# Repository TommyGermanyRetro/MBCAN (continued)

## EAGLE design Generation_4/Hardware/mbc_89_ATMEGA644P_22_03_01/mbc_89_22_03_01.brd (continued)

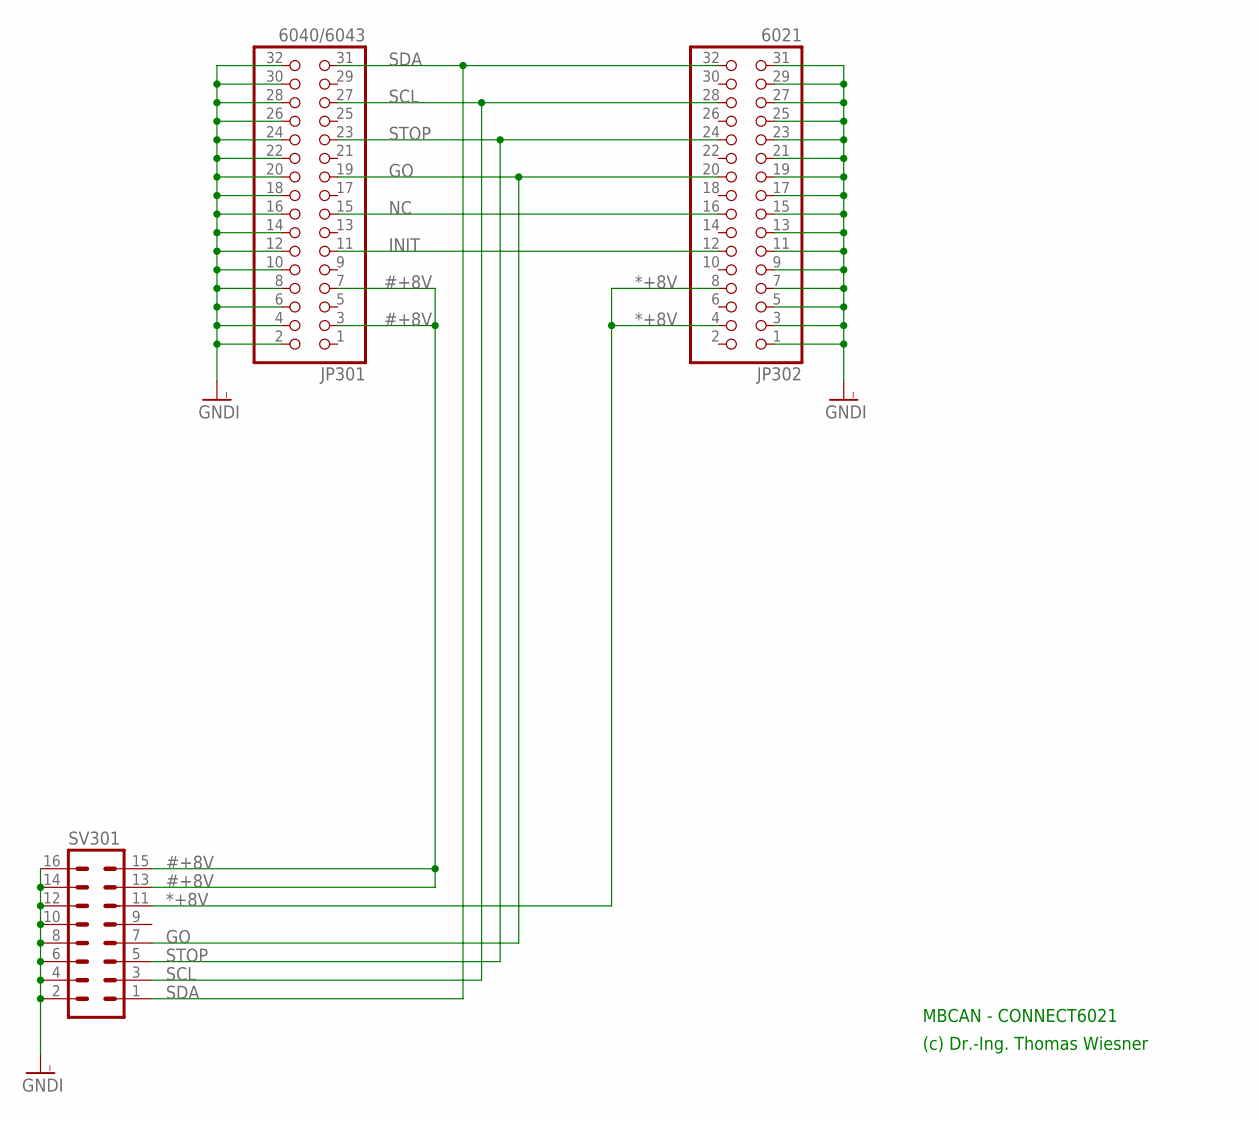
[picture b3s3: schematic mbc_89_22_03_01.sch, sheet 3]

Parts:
JP301: 6040/6043; 2X16
JP302: 6021; 2X16
SV301: ML16

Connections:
#+8V: JP301.3, JP301.7, SV301.13, SV301.15
*+8V: JP302.4, JP302.8, SV301.11
GNDI: JP301.2, JP301.4, JP301.6, JP301.8, JP301.10, JP301.12, JP301.14, JP301.16, JP301.18, JP301.20, JP301.22, JP301.24, JP301.26, JP301.28, JP301.30, JP301.32, JP302.1, JP302.3, JP302.5, JP302.7, JP302.9, JP302.11, JP302.13, JP302.15, JP302.17, JP302.19, JP302.21, JP302.23, JP302.25, JP302.27, JP302.29, JP302.31, SV301.2, SV301.4, SV301.6, SV301.8, SV301.10, SV301.12, SV301.14, SV301.16
GO: JP301.19, JP302.20, SV301.7
INIT: JP301.11, JP302.12
NC: JP301.15, JP302.16
SCL: JP301.27, JP302.28, SV301.3
SDA: JP301.31, JP302.32, SV301.1
STOP: JP301.23, JP302.24, SV301.5

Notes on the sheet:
(c) Dr.-Ing. Thomas Wiesner
MBCAN - CONNECT6021

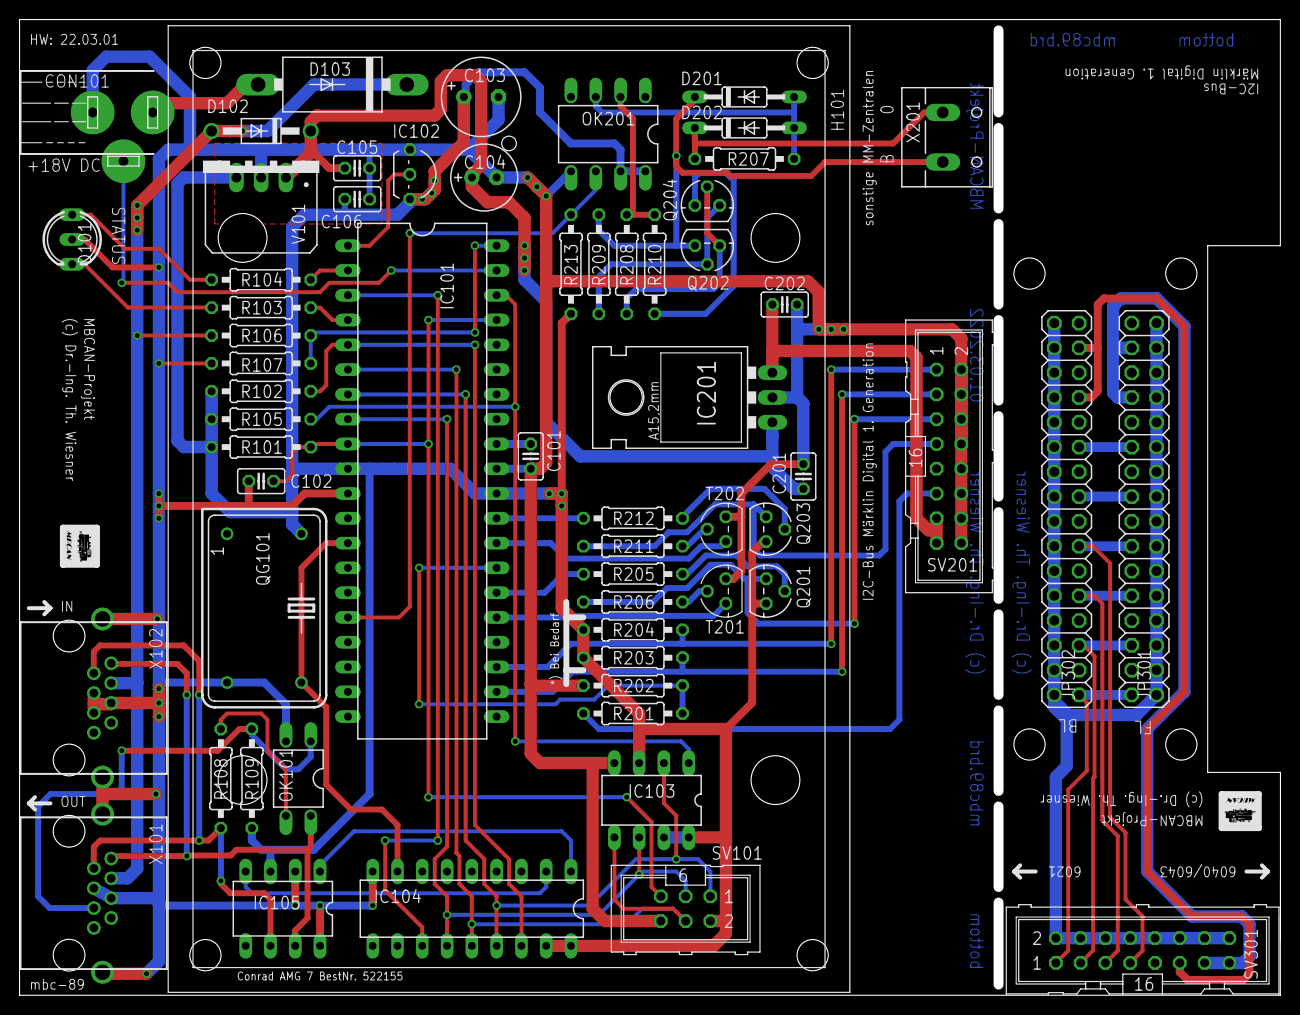
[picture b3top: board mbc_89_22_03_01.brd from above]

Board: 2 copper layers, 129.2 x 100.0 mm, 61 parts (0 on the bottom side), 59 nets.

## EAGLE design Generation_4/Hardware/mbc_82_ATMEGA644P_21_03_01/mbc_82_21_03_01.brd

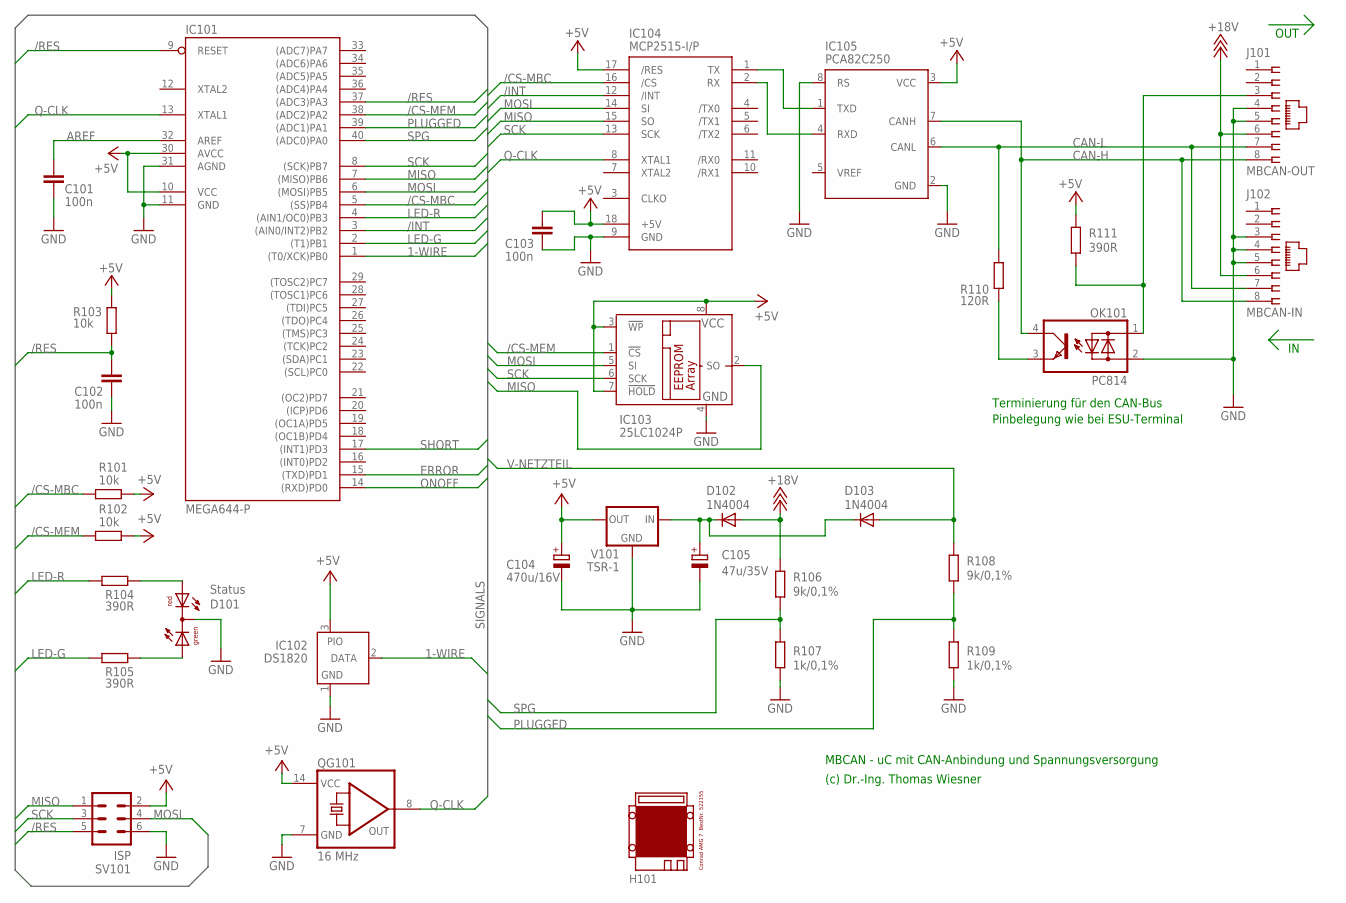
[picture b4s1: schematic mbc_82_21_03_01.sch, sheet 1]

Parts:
C101, C102, C103: 100n; C025-025X050
C104: 470u/16V; E3,5-8
C105: 47u/35V; E2,5-7
D101: Status; DUOLED5MM
D102, D103: 1N4004; DO41-10
H101: MODULGEHÄUSE-AMG-7
IC101: MEGA644-P; DIL40
IC102: DS1820; TO92-
IC103: 25LC1024P; DIL8
IC104: MCP2515-I/P; DIL18
IC105: PCA82C250; DIL08
J101: MBCAN-OUT; 215877-4
J102: MBCAN-IN; 215877-4
OK101: PC814; DIL04
QG101: 16 MHz; DIL14S
R101, R102, R103: 10k; 0207/10
R104, R105, R111: 390R; 0207/10
R106, R108: 9k/0,1%; 0207/10
R107, R109: 1k/0,1%; 0207/10
R110: 120R; 0207/10
SV101: ISP; ML6
V101: TSR-1; TRACO-TSR-1

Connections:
1-WIRE: IC101.1 ((T0/XCK)PB0), IC102.2 (DATA)
+5V: C103.1, C104.+, IC101.10 (VCC), IC101.30 (AVCC), IC102.3 (PIO), IC103.3 (!WP), IC103.7 (!HOLD), IC103.8 (VCC), IC104.17 (/RES), IC104.18 (+5V), IC105.3 (VCC), QG101.14 (VCC), R101.2, R102.1, R103.2, R111.1, SV101.2, V101.OUT; also elsewhere on the board
+18V: D102.A, J101.6, J102.6, R106.1
/CS-MBC: IC101.5 ((SS)PB4), IC104.16 (/CS), R101.1
/CS-MEM: IC101.38 ((ADC2)PA2), IC103.1 (!CS), R102.2
/INT: IC101.3 ((AIN0/INT2)PB2), IC104.12 (/INT)
/RES: C102.1, IC101.9 (RESET), IC101.37 ((ADC3)PA3), R103.1, SV101.5
AREF: C101.1, IC101.32 (AREF)
CAN-H: IC105.7 (CANH), J101.8, J102.8, OK101.4 (C)
CAN-L: IC105.6 (CANL), J101.7, J102.7, R110.2
ERROR: IC101.15 ((TXD)PD1); also elsewhere on the board
GND: C101.2, C102.2, C103.2, C104.-, C105.-, D101.K (C), IC101.11 (GND), IC101.31 (AGND), IC102.1 (GND), IC103.4 (GND), IC104.9 (GND), IC105.2 (GND), IC105.8 (RS), J101.4, J101.5, J102.3, J102.4, J102.5, OK101.2 (AC2), QG101.7 (GND), R107.2, R109.2, SV101.6, V101.GND; also elsewhere on the board
LED-G: IC101.2 ((T1)PB1), R105.1
LED-R: IC101.4 ((AIN1/OC0)PB3), R104.1
MISO: IC101.7 ((MISO)PB6), IC103.2 (SO), IC104.15 (SO), SV101.1
MOSI: IC101.6 ((MOSI)PB5), IC103.5 (SI), IC104.14 (SI), SV101.4
unnamed: IC104.1 (TX), IC105.1 (TXD)
unnamed: IC104.2 (RX), IC105.4 (RXD)
unnamed: OK101.3 (E), R110.1
unnamed: J101.3, OK101.1 (AC1), R111.2
unnamed: C105.+, D102.C, D103.C, V101.IN
unnamed: D101.AR, R104.2
unnamed: D101.AG, R105.2
ONOFF: IC101.14 ((RXD)PD0); also elsewhere on the board
PLUGGED: IC101.39 ((ADC1)PA1), R108.2, R109.1
Q-CLK: IC101.13 (XTAL1), IC104.8 (XTAL1), QG101.8 (OUT)
SCK: IC101.8 ((SCK)PB7), IC103.6 (SCK), IC104.13 (SCK), SV101.3
SHORT: IC101.17 ((INT1)PD3); also elsewhere on the board
SPG: IC101.40 ((ADC0)PA0), R106.2, R107.1
V-NETZTEIL: D103.A, R108.1; also elsewhere on the board

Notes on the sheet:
MBCAN - uC mit CAN-Anbindung und Spannungsversorgung
(c) Dr.-Ing. Thomas Wiesner
Terminierung für den CAN-Bus
Pinbelegung wie bei ESU-Terminal
OUT

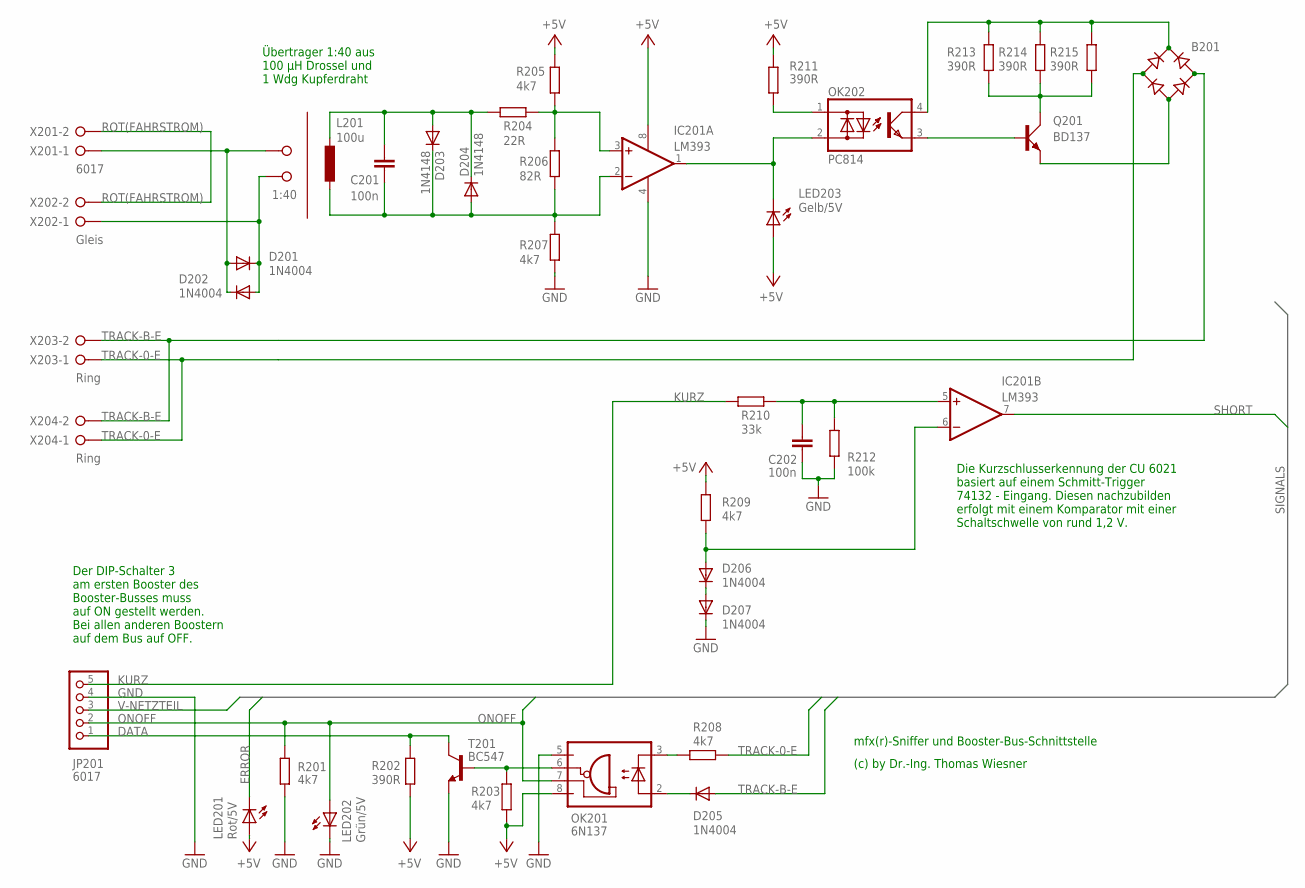
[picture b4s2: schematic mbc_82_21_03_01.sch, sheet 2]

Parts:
B201: RB1A
C201, C202: 100n; C025-025X050
D201, D202, D205, D206, D207: 1N4004; DO41-10
D203, D204: 1N4148; DO35-10
IC201: LM393; DIL08
JP201: 6017; 1X05
L201: 100u; 6000-XXXX-RC
LED201: Rot/5V; LED3MM
LED202: Grün/5V; LED3MM
LED203: Gelb/5V; LED3MM
OK201: 6N137; DIL08
OK202: PC814; DIL04
Q201: BD137; TO126AV
R201, R203, R205, R207, R208, R209: 4k7; 0207/10
R202, R211, R213, R214, R215: 390R; 0207/10
R204: 22R; 0207/10
R206: 82R; 0207/10
R210: 33k; 0207/10
R212: 100k; 0207/10
T201: BC547; TO92
TP: 1:40; W237-132
X201: 6017; W237-132
X202: Gleis; W237-132
X203, X204: Ring; W237-132

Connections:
+5V: IC201.8 (V+), LED201.A, LED203.A, OK201.8 (VCC), R202.1, R203.1, R205.2, R209.2, R211.2; also elsewhere on the board
DATA: JP201.1, R202.2, T201.3 (C)
ERROR: LED201.K (C); also elsewhere on the board
GND: C202.2, D207.C, IC201.4 (V-), JP201.4, LED202.K (C), OK201.5 (GND), R201.2, R207.2, R212.2, T201.1 (E); also elsewhere on the board
KURZ: JP201.5, R210.2
unnamed: OK202.3 (E), Q201.B
unnamed: D205.C, OK201.2 (A)
unnamed: OK201.3 (C), R208.1
unnamed: B201.-, Q201.E
unnamed: C201.2, D203.C, D204.A, IC201.2 (-IN), L201.2, R206.2, R207.1
unnamed: IC201.3 (+IN), R204.2, R205.1, R206.1
unnamed: D201.C, D202.A, TP.1, X202.1
unnamed: B201.+, OK202.4 (C), R213.1, R214.1, R215.1
unnamed: Q201.C, R213.2, R214.2, R215.2
unnamed: C201.1, D203.A, D204.C, L201.1, R204.1
unnamed: D206.C, D207.A
unnamed: OK202.1 (AC1), R211.1
unnamed: IC201.1 (COLOUT), LED203.K (C), OK202.2 (AC2)
unnamed: D206.A, IC201.6 (-IN), R209.1
unnamed: C202.1, IC201.5 (+IN), R210.1, R212.1
unnamed: OK201.6 (VO), R203.2, T201.2 (B)
O': D201.A, D202.C, TP.2, X201.1
ONOFF: JP201.2, LED202.A, OK201.7 (VE), R201.1; also elsewhere on the board
ROT(FAHRSTROM): X201.2, X202.2
SHORT: IC201.7 (COLOUT); also elsewhere on the board
TRACK-0-E: B201.AC1, R208.2, X203.1, X204.1
TRACK-B-E: B201.AC2, D205.A, X203.2, X204.2
V-NETZTEIL: JP201.3; also elsewhere on the board

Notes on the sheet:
Übertrager 1:40 aus 100 µH Drossel und 1 Wdg Kupferdraht
mfx(r)-Sniffer und Booster-Bus-Schnittstelle
(c) by Dr.-Ing. Thomas Wiesner
Der DIP-Schalter 3 am ersten Booster des Booster-Busses muss auf ON gestellt werden. Bei allen anderen Boostern auf dem Bus auf OFF.
Die Kurzschlusserkennung der CU 6021 basiert auf einem Schmitt-Trigger 74132 - Eingang. Diesen nachzubilden erfolgt mit einem Komparator mit einer Schaltschwelle von rund 1,2 V.

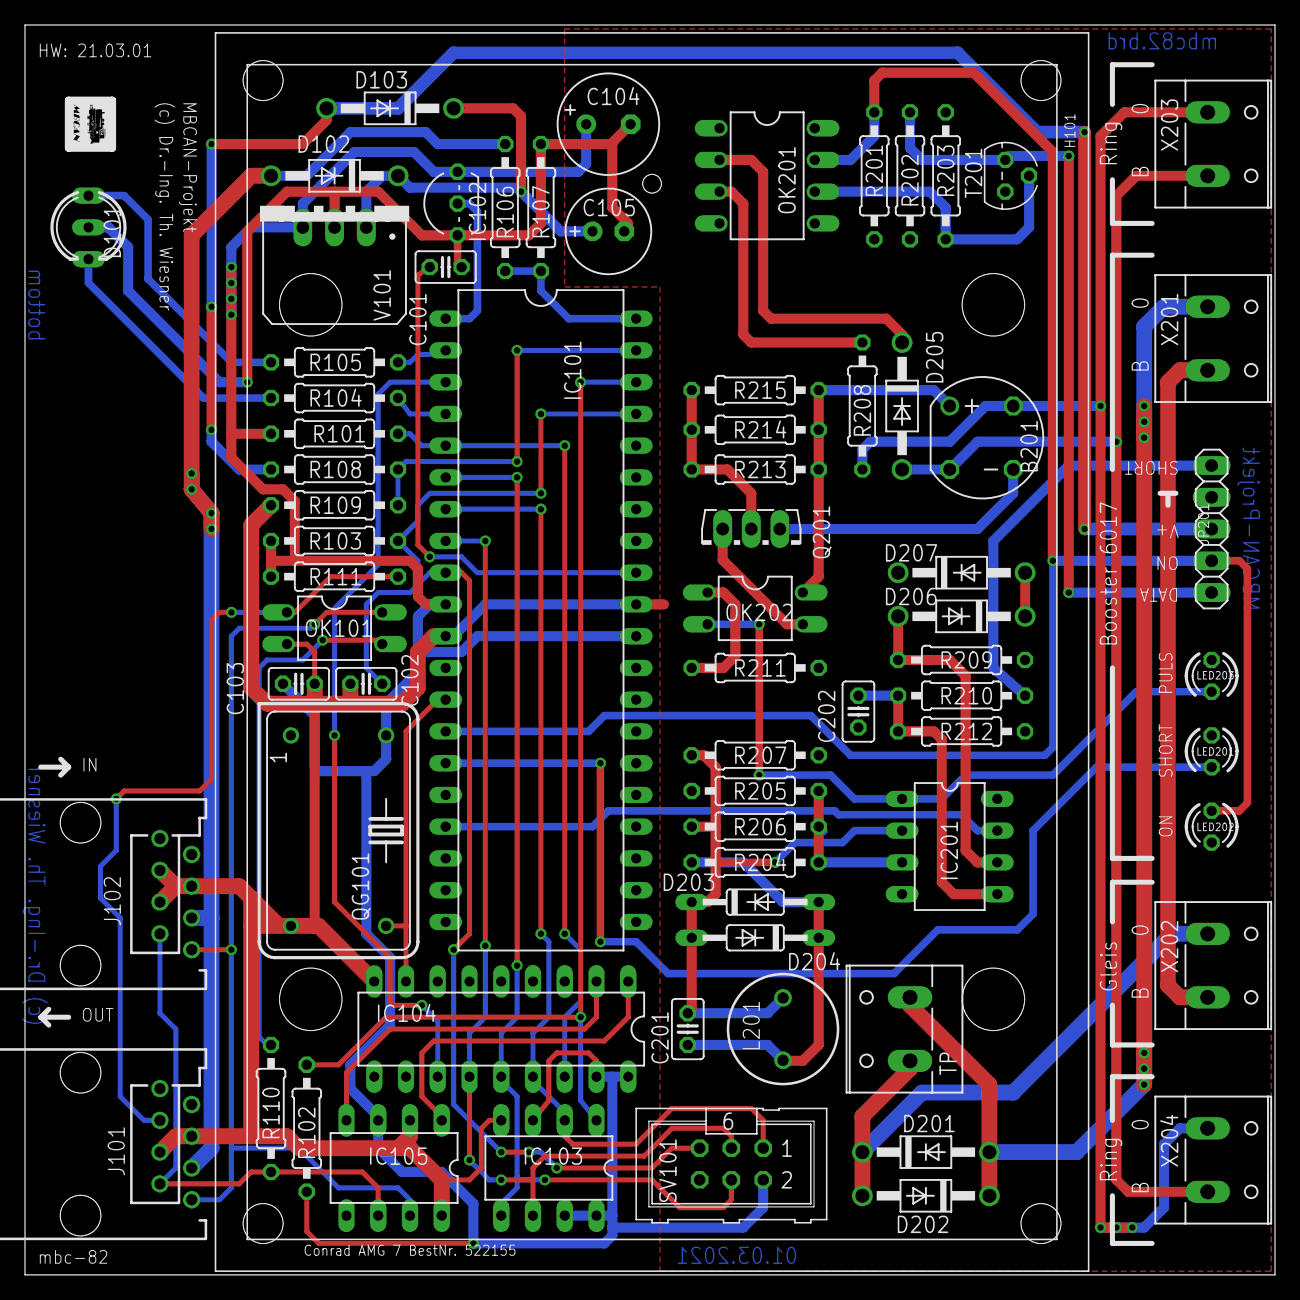
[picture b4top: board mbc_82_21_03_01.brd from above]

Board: 2 copper layers, 100.0 x 100.0 mm, 71 parts (0 on the bottom side), 52 nets.

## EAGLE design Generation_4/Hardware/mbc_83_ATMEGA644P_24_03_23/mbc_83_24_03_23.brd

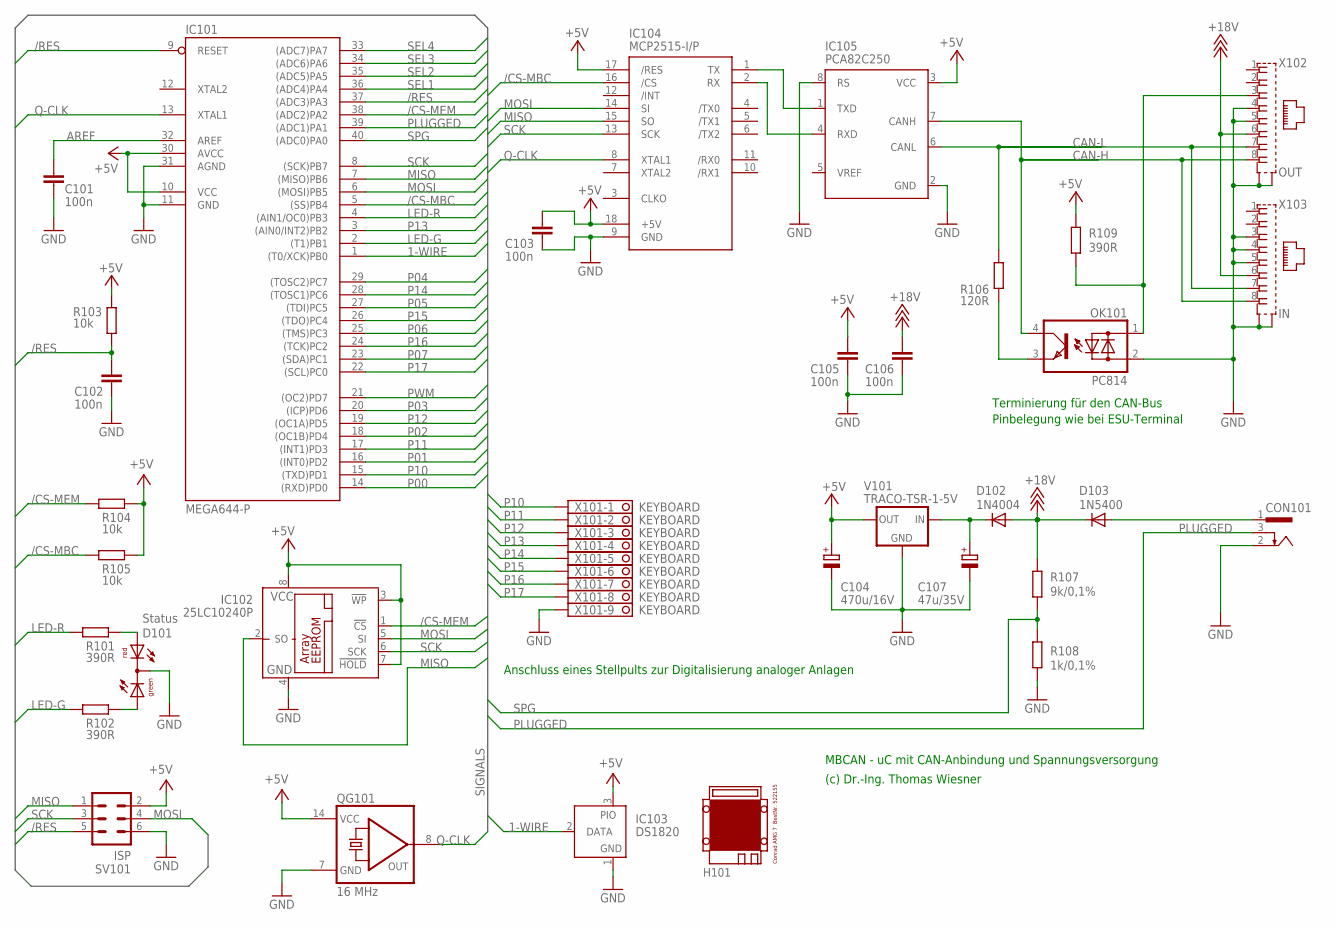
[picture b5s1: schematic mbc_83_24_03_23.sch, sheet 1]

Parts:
C101, C102, C103, C105, C106: 100n; C025-025X050
C104: 470u/16V; E3,5-8
C107: 47u/35V; E2,5-7
CON101: POWER-JACK
D101: Status; DUOLED5MM
D102: 1N4004; DO41-10
D103: 1N5400; DO201-15
H101: MODULGEHÄUSE-AMG-7
IC101: MEGA644-P; DIL40
IC102: 25LC10240P; DIL8
IC103: DS1820; TO92-
IC104: MCP2515-I/P; DIL18
IC105: PCA82C250; DIL08
OK101: PC814; DIL04
QG101: 16 MHz; DIL14S
R101, R102, R109: 390R; 0207/10
R103, R104, R105: 10k; 0207/10
R106: 120R; 0207/10
R107: 9k/0,1%; 0207/10
R108: 1k/0,1%; 0207/10
SV101: ISP; ML6
V101: TRACO-TSR-1-5V; TRACO-TSR-1
X101: KEYBOARD; 1751316
X102: OUT; 0446200002
X103: IN; 0446200002

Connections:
1-WIRE: IC101.1 ((T0/XCK)PB0), IC103.2 (DATA)
+5V: C103.1, C104.+, C105.1, IC101.10 (VCC), IC101.30 (AVCC), IC102.3 (!WP), IC102.7 (!HOLD), IC102.8 (VCC), IC103.3 (PIO), IC104.17 (/RES), IC104.18 (+5V), IC105.3 (VCC), QG101.14 (VCC), R103.2, R104.2, R105.2, R109.1, SV101.2, V101.OUT; also elsewhere on the board
+18V: C106.1, D102.A, D103.C, R107.1, X102.6, X103.6; also elsewhere on the board
/CS-MBC: IC101.5 ((SS)PB4), IC104.16 (/CS), R105.1
/CS-MEM: IC101.38 ((ADC2)PA2), IC102.1 (!CS), R104.1
/RES: C102.1, IC101.9 (RESET), IC101.37 ((ADC3)PA3), R103.1, SV101.5
AREF: C101.1, IC101.32 (AREF)
CAN-H: IC105.7 (CANH), OK101.4 (C), X102.8, X103.8
CAN-L: IC105.6 (CANL), R106.2, X102.7, X103.7
GND: C101.2, C102.2, C103.2, C104.-, C105.2, C106.2, C107.-, CON101.2, D101.K (C), IC101.11 (GND), IC101.31 (AGND), IC102.4 (GND), IC103.1 (GND), IC104.9 (GND), IC105.2 (GND), IC105.8 (RS), OK101.2 (AC2), QG101.7 (GND), R108.2, SV101.6, V101.GND, X101.9, X102.4, X102.5, X102.S@1 (S1), X102.S@2 (S2), X103.3, X103.4, X103.5, X103.S@1 (S1), X103.S@2 (S2); also elsewhere on the board
LED-G: IC101.2 ((T1)PB1), R102.1
LED-R: IC101.4 ((AIN1/OC0)PB3), R101.1
MISO: IC101.7 ((MISO)PB6), IC102.2 (SO), IC104.15 (SO), SV101.1
MOSI: IC101.6 ((MOSI)PB5), IC102.5 (SI), IC104.14 (SI), SV101.4
unnamed: IC104.1 (TX), IC105.1 (TXD)
unnamed: IC104.2 (RX), IC105.4 (RXD)
unnamed: OK101.3 (E), R106.1
unnamed: OK101.1 (AC1), R109.2, X102.3
unnamed: C107.+, D102.C, V101.IN
unnamed: D101.AR, R101.2
unnamed: D101.AG, R102.2
P00: IC101.14 ((RXD)PD0); also elsewhere on the board
P01: IC101.16 ((INT0)PD2); also elsewhere on the board
P02: IC101.18 ((OC1B)PD4); also elsewhere on the board
P03: IC101.20 ((ICP)PD6); also elsewhere on the board
P04: IC101.29 ((TOSC2)PC7); also elsewhere on the board
P05: IC101.27 ((TDI)PC5); also elsewhere on the board
P06: IC101.25 ((TMS)PC3); also elsewhere on the board
P07: IC101.23 ((SDA)PC1); also elsewhere on the board
P10: IC101.15 ((TXD)PD1), X101.1
P11: IC101.17 ((INT1)PD3), X101.2
P12: IC101.19 ((OC1A)PD5), X101.3
P13: IC101.3 ((AIN0/INT2)PB2), X101.4
P14: IC101.28 ((TOSC1)PC6), X101.5
P15: IC101.26 ((TDO)PC4), X101.6
P16: IC101.24 ((TCK)PC2), X101.7
P17: IC101.22 ((SCL)PC0), X101.8
PLUGGED: CON101.3, IC101.39 ((ADC1)PA1)
PWM: IC101.21 ((OC2)PD7); also elsewhere on the board
Q-CLK: IC101.13 (XTAL1), IC104.8 (XTAL1), QG101.8 (OUT)
SCK: IC101.8 ((SCK)PB7), IC102.6 (SCK), IC104.13 (SCK), SV101.3
SEL1: IC101.36 ((ADC4)PA4); also elsewhere on the board
SEL2: IC101.35 ((ADC5)PA5); also elsewhere on the board
SEL3: IC101.34 ((ADC6)PA6); also elsewhere on the board
SEL4: IC101.33 ((ADC7)PA7); also elsewhere on the board
SPG: IC101.40 ((ADC0)PA0), R107.2, R108.1
V-NETZTEIL1: CON101.1, D103.A

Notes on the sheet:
MBCAN - uC mit CAN-Anbindung und Spannungsversorgung
(c) Dr.-Ing. Thomas Wiesner
Terminierung für den CAN-Bus
Pinbelegung wie bei ESU-Terminal
Anschluss eines Stellpults zur Digitalisierung analoger Anlagen

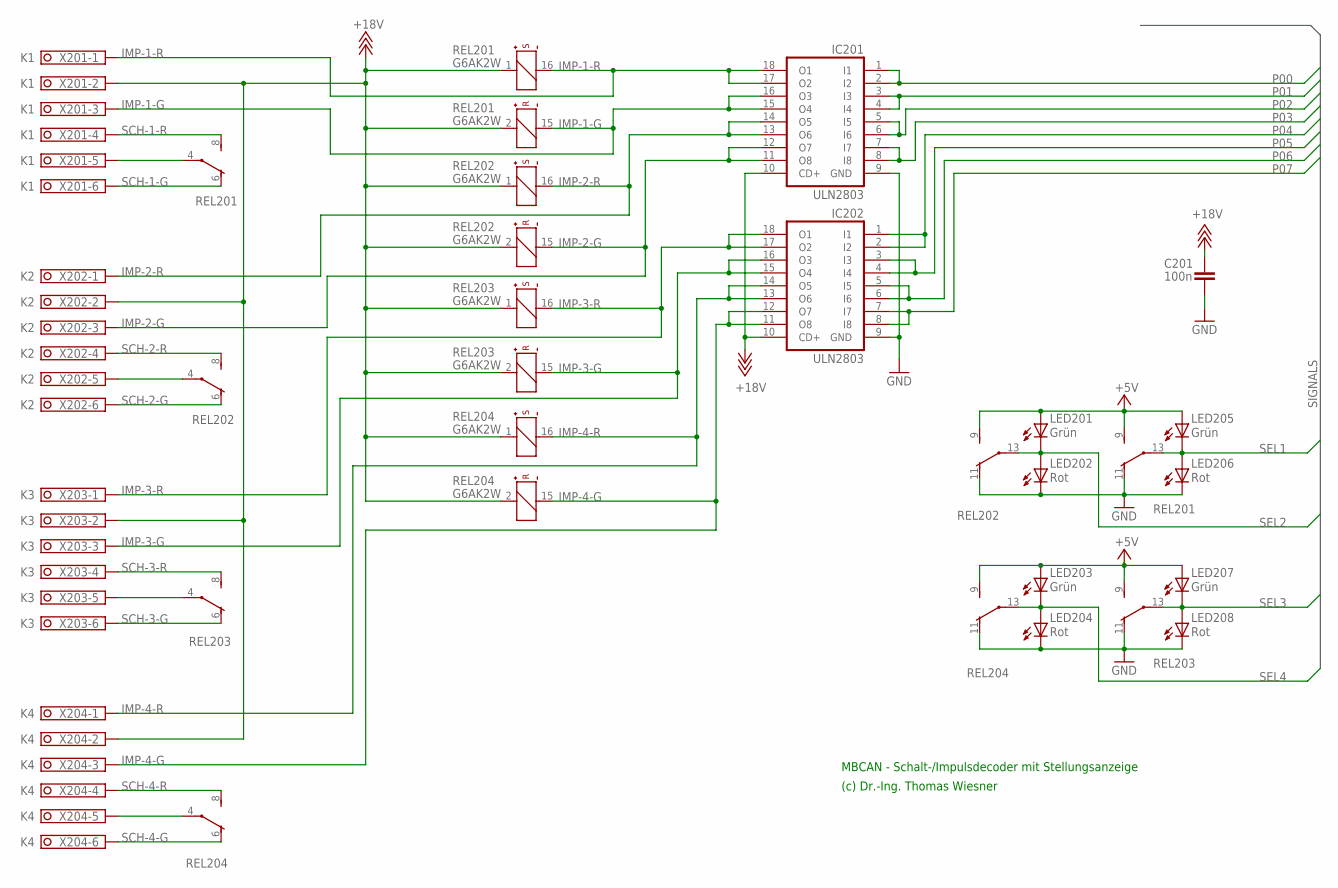
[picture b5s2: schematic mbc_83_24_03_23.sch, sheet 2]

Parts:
C201: 100n; C025-025X050
IC201, IC202: ULN2803; DIL18
LED201, LED203, LED205, LED207: Grün; LED3MM
LED202, LED204, LED206, LED208: Rot; LED3MM
REL201, REL202, REL203, REL204: G6AK2W; REL-BIPOLAR
X201: K1; 1751280
X202: K2; 1751280
X203: K3; 1751280
X204: K4; 1751280

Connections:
+5V: LED201.A, LED203.A, LED205.A, LED207.A, REL201.9 (S), REL202.9 (S), REL203.9 (S), REL204.9 (S); also elsewhere on the board
+18V: C201.1, IC201.10 (CD+), IC202.10 (CD+), REL201.1 (+), REL201.2 (+), REL202.1 (+), REL202.2 (+), REL203.1 (+), REL203.2 (+), REL204.1 (+), REL204.2 (+), X201.2, X202.2, X203.2, X204.2; also elsewhere on the board
GND: C201.2, IC201.9 (GND), IC202.9 (GND), LED202.K (C), LED204.K (C), LED206.K (C), LED208.K (C), REL201.11 (O), REL202.11 (O), REL203.11 (O), REL204.11 (O); also elsewhere on the board
IMP-1-G: IC201.15 (O4), IC201.16 (O3), REL201.15 (-), X201.3; also elsewhere on the board
IMP-1-R: IC201.17 (O2), IC201.18 (O1), REL201.16 (-), X201.1; also elsewhere on the board
IMP-2-G: IC201.11 (O8), IC201.12 (O7), REL202.15 (-), X202.3; also elsewhere on the board
IMP-2-R: IC201.13 (O6), IC201.14 (O5), REL202.16 (-), X202.1; also elsewhere on the board
IMP-3-G: IC202.15 (O4), IC202.16 (O3), REL203.15 (-), X203.3; also elsewhere on the board
IMP-3-R: IC202.17 (O2), IC202.18 (O1), REL203.16 (-), X203.1; also elsewhere on the board
IMP-4-G: IC202.11 (O8), IC202.12 (O7), REL204.15 (-), X204.3; also elsewhere on the board
IMP-4-R: IC202.13 (O6), IC202.14 (O5), REL204.16 (-), X204.1; also elsewhere on the board
unnamed: REL202.4, X202.5
unnamed: REL201.4, X201.5
unnamed: REL203.4, X203.5
unnamed: REL204.4, X204.5
P00: IC201.1 (I1), IC201.2 (I2); also elsewhere on the board
P01: IC201.3 (I3), IC201.4 (I4); also elsewhere on the board
P02: IC201.5 (I5), IC201.6 (I6); also elsewhere on the board
P03: IC201.7 (I7), IC201.8 (I8); also elsewhere on the board
P04: IC202.1 (I1), IC202.2 (I2); also elsewhere on the board
P05: IC202.3 (I3), IC202.4 (I4); also elsewhere on the board
P06: IC202.5 (I5), IC202.6 (I6); also elsewhere on the board
P07: IC202.7 (I7), IC202.8 (I8); also elsewhere on the board
SCH-1-G: REL201.6 (O), X201.6; also elsewhere on the board
SCH-1-R: REL201.8 (S), X201.4
SCH-2-G: REL202.6 (O), X202.6; also elsewhere on the board
SCH-2-R: REL202.8 (S), X202.4
SCH-3-G: REL203.6 (O), X203.6; also elsewhere on the board
SCH-3-R: REL203.8 (S), X203.4
SCH-4-G: REL204.6 (O), X204.6; also elsewhere on the board
SCH-4-R: REL204.8 (S), X204.4
SEL1: LED205.K (C), LED206.A, REL201.13; also elsewhere on the board
SEL2: LED201.K (C), LED202.A, REL202.13; also elsewhere on the board
SEL3: LED207.K (C), LED208.A, REL203.13; also elsewhere on the board
SEL4: LED203.K (C), LED204.A, REL204.13; also elsewhere on the board

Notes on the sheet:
MBCAN - Schalt-/Impulsdecoder mit Stellungsanzeige
(c) Dr.-Ing. Thomas Wiesner

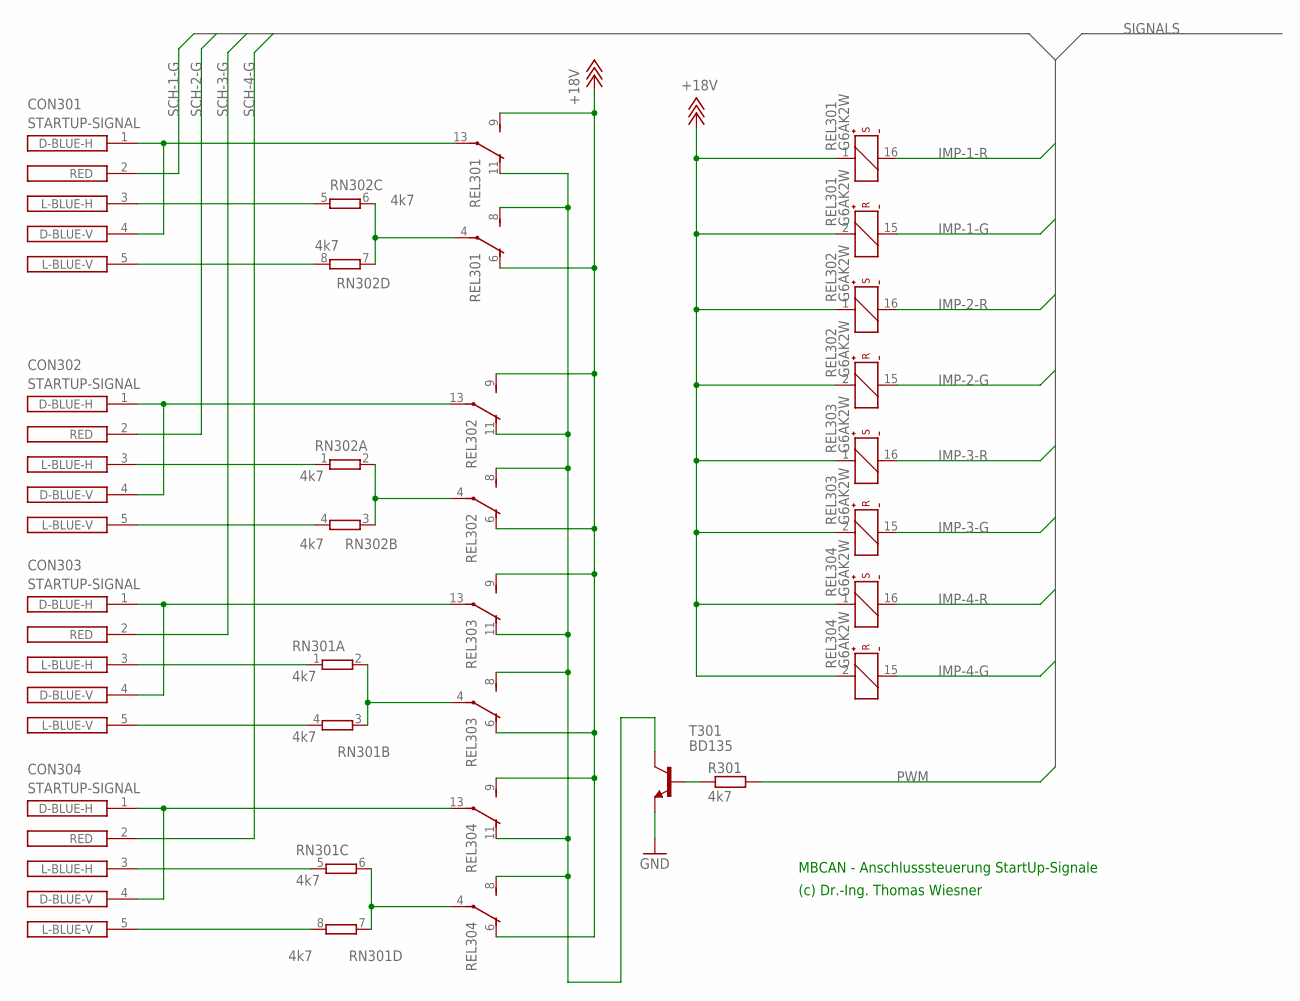
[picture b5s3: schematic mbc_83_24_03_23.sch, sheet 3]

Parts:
CON301, CON302, CON303, CON304: STARTUP-SIGNAL; SIGNAL-MAIN
R301: 4k7; 0207/10
REL301, REL302, REL303, REL304: G6AK2W; REL-BIPOLAR
RN301, RN302: 4k7; SIL8
T301: BD135; TO126V

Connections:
+18V: REL301.1 (+), REL301.2 (+), REL301.6 (O), REL301.9 (S), REL302.1 (+), REL302.2 (+), REL302.6 (O), REL302.9 (S), REL303.1 (+), REL303.2 (+), REL303.6 (O), REL303.9 (S), REL304.1 (+), REL304.2 (+), REL304.6 (O), REL304.9 (S); also elsewhere on the board
GND: T301.1 (E); also elsewhere on the board
IMP-1-G: REL301.15 (-); also elsewhere on the board
IMP-1-R: REL301.16 (-); also elsewhere on the board
IMP-2-G: REL302.15 (-); also elsewhere on the board
IMP-2-R: REL302.16 (-); also elsewhere on the board
IMP-3-G: REL303.15 (-); also elsewhere on the board
IMP-3-R: REL303.16 (-); also elsewhere on the board
IMP-4-G: REL304.15 (-); also elsewhere on the board
IMP-4-R: REL304.16 (-); also elsewhere on the board
unnamed: CON302.5 (L-BLUE-V), RN302.4 (2)
unnamed: CON301.1 (D-BLUE-H), CON301.4 (D-BLUE-V), REL301.13
unnamed: CON301.5 (L-BLUE-V), RN302.8 (2)
unnamed: CON303.5 (L-BLUE-V), RN301.4 (2)
unnamed: CON304.5 (L-BLUE-V), RN301.8 (2)
unnamed: R301.1, T301.3 (B)
unnamed: REL301.8 (S), REL301.11 (O), REL302.8 (S), REL302.11 (O), REL303.8 (S), REL303.11 (O), REL304.8 (S), REL304.11 (O), T301.2 (C)
unnamed: CON302.1 (D-BLUE-H), CON302.4 (D-BLUE-V), REL302.13
unnamed: CON302.3 (L-BLUE-H), RN302.1
unnamed: CON304.1 (D-BLUE-H), CON304.4 (D-BLUE-V), REL304.13
unnamed: CON304.3 (L-BLUE-H), RN301.5 (1)
unnamed: CON303.1 (D-BLUE-H), CON303.4 (D-BLUE-V), REL303.13
unnamed: CON301.3 (L-BLUE-H), RN302.5 (1)
unnamed: CON303.3 (L-BLUE-H), RN301.1
unnamed: REL301.4, RN302.6 (2), RN302.7 (1)
unnamed: REL302.4, RN302.2, RN302.3 (1)
unnamed: REL303.4, RN301.2, RN301.3 (1)
unnamed: REL304.4, RN301.6 (2), RN301.7 (1)
PWM: R301.2; also elsewhere on the board
SCH-1-G: CON301.2 (RED); also elsewhere on the board
SCH-2-G: CON302.2 (RED); also elsewhere on the board
SCH-3-G: CON303.2 (RED); also elsewhere on the board
SCH-4-G: CON304.2 (RED); also elsewhere on the board

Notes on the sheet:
MBCAN - Anschlusssteuerung StartUp-Signale
(c) Dr.-Ing. Thomas Wiesner

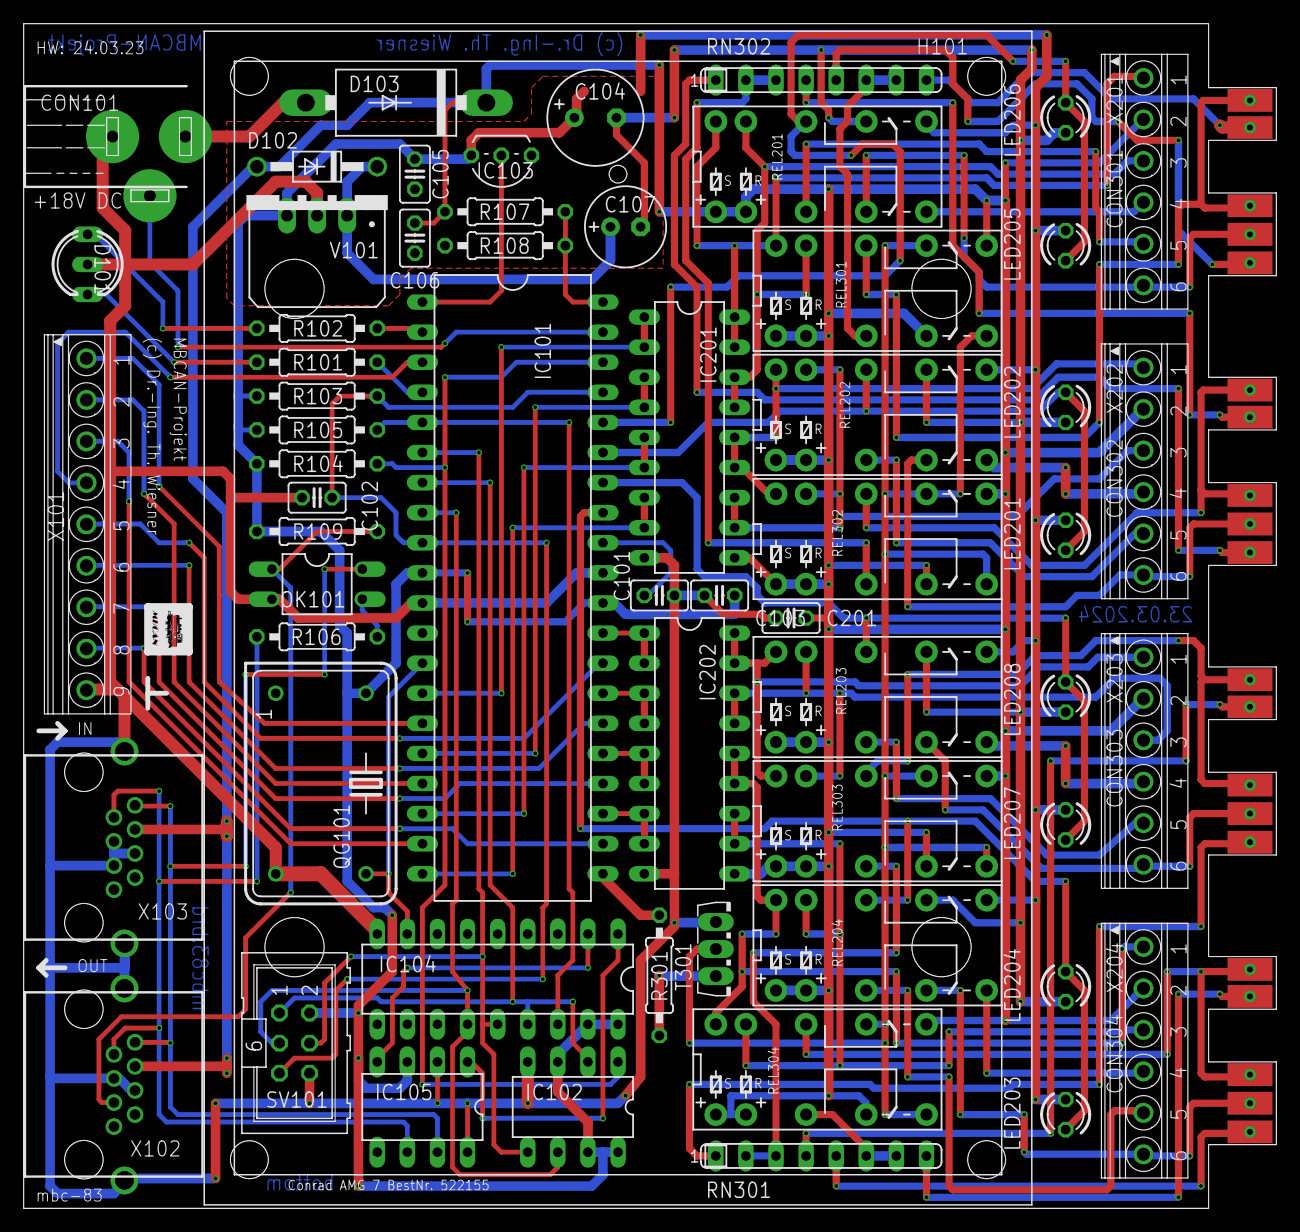
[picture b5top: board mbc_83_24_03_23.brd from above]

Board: 2 copper layers, 105.7 x 100.0 mm, 64 parts (0 on the bottom side), 85 nets.
